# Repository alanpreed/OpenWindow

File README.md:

# OpenWindow
OpenWindow is a project that aims to create an open-source electric window controller for my car.

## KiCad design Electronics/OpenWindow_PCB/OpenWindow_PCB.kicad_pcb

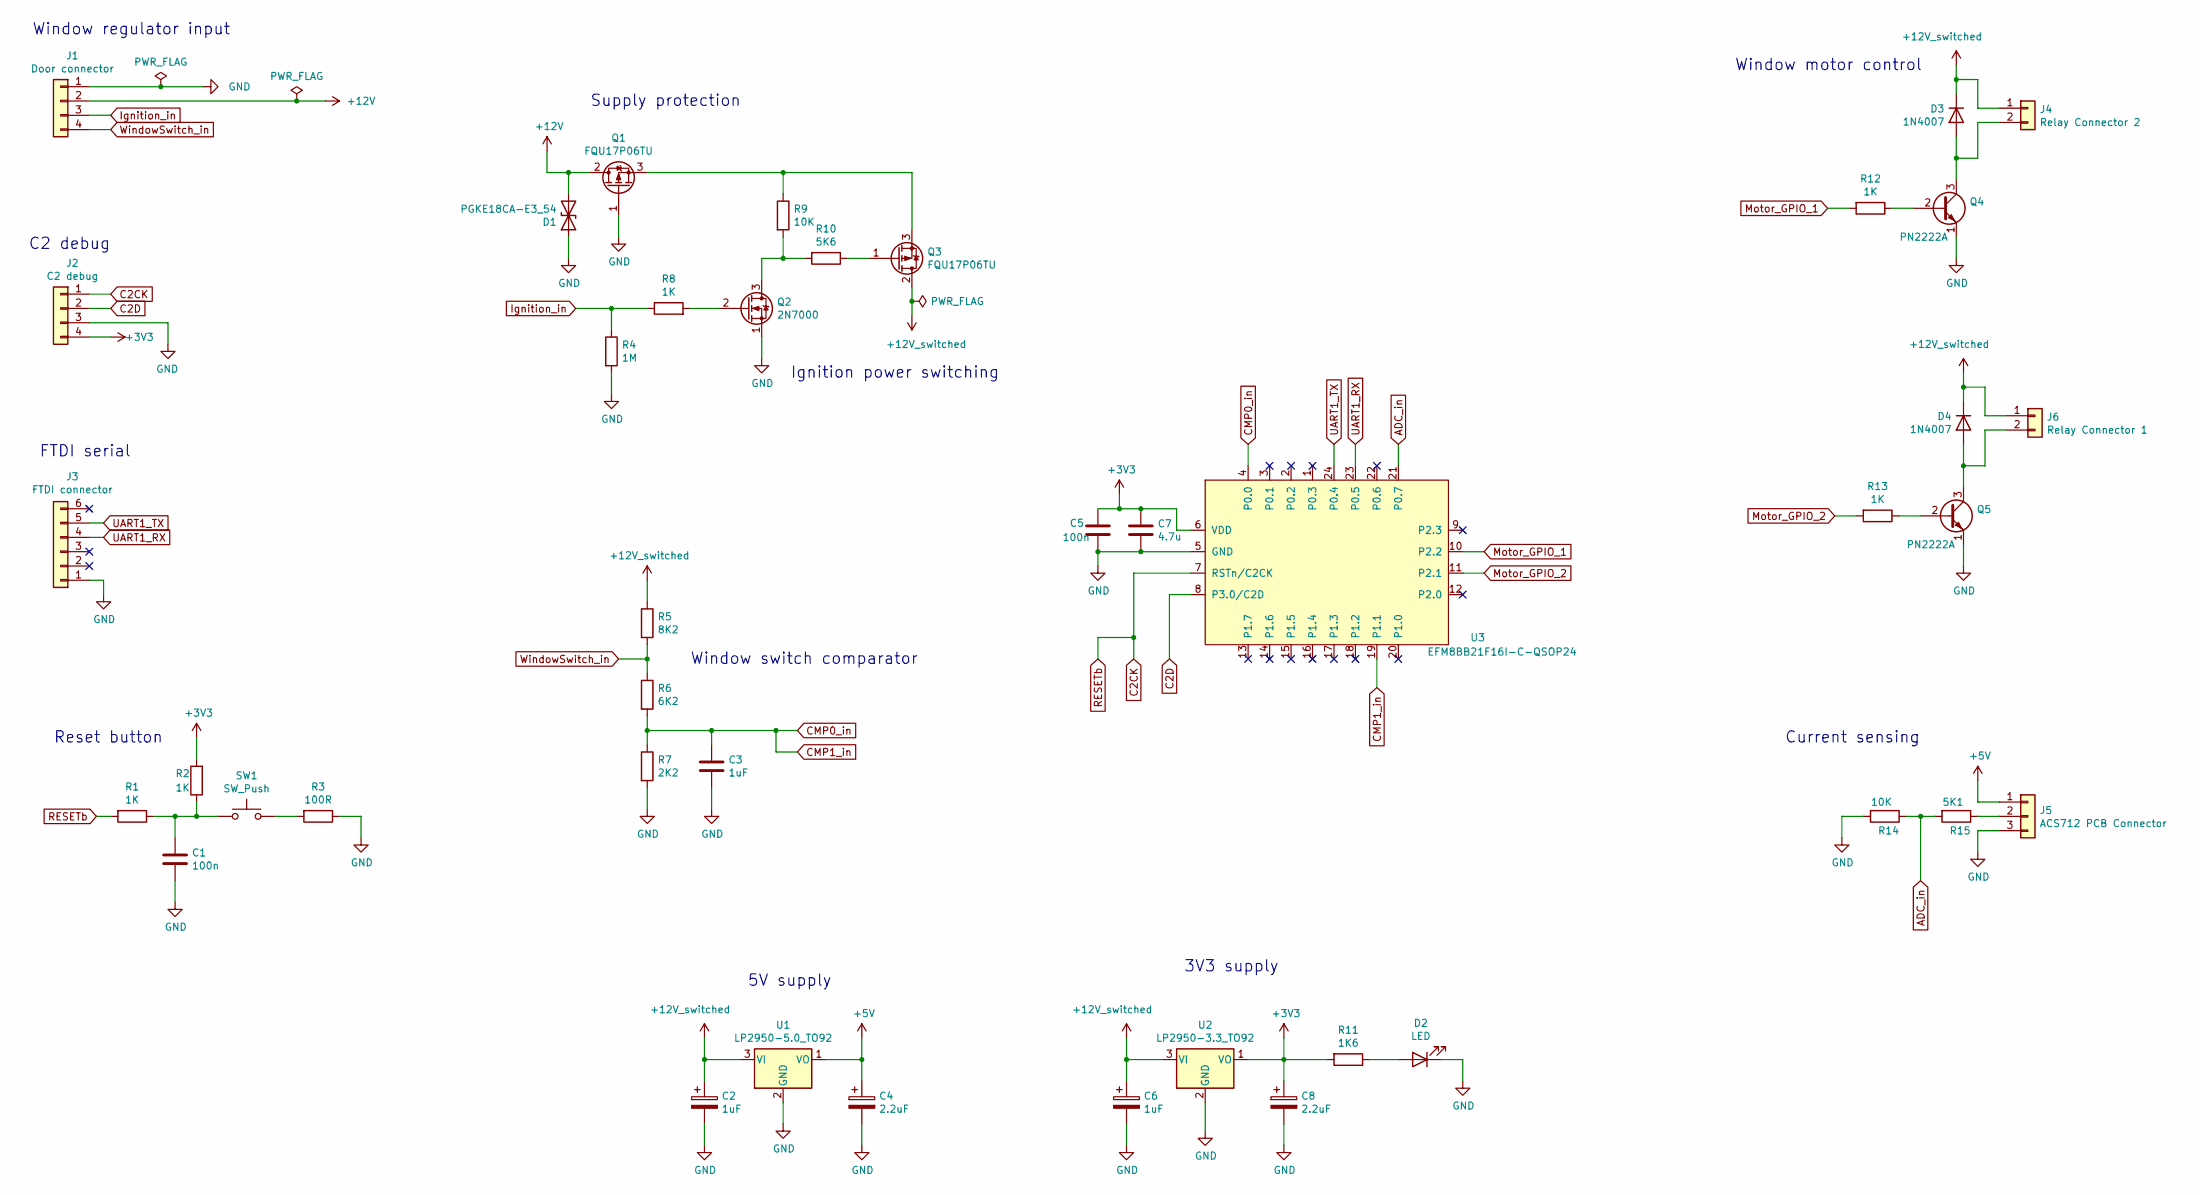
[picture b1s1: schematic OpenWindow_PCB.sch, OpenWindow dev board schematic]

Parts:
C1, C5: 100n; C_0805_2012Metric_Pad1.18x1.45mm_HandSolder
C2, C3, C6: 1uF; CP_Radial_D5.0mm_P2.00mm
C4, C8: 2.2uF; CP_Radial_D5.0mm_P2.00mm
C7: 4.7u; C_0805_2012Metric_Pad1.18x1.45mm_HandSolder
D1: PGKE18CA-E3_54; D_DO-15_P12.70mm_Horizontal
D2: LED; LED_D3.0mm
D3, D4: 1N4007; D_DO-41_SOD81_P10.16mm_Horizontal
J1: Door connector; JST_XH_B4B-XH-AM_1x04_P2.50mm_Vertical
J2: C2 debug; PinHeader_1x04_P2.54mm_Vertical
J3: FTDI connector; PinHeader_1x06_P2.54mm_Vertical
J4: Relay Connector 2; TerminalBlock_Phoenix_MKDS-3-2-5.08_1x02_P5.08mm_Horizontal
J5: ACS712 PCB Connector; JST_XH_B3B-XH-A_1x03_P2.50mm_Vertical
J6: Relay Connector 1; TerminalBlock_Phoenix_MKDS-3-2-5.08_1x02_P5.08mm_Horizontal
Q1, Q3: FQU17P06TU; TO-251-3_Vertical
Q2: 2N7000; TO-92_Inline
Q4, Q5: PN2222A; TO-92_Inline
R1, R2: 1K; R_0603_1608Metric_Pad0.98x0.95mm_HandSolder
R3: 100R; R_0603_1608Metric_Pad0.98x0.95mm_HandSolder
R4: 1M; R_Axial_DIN0411_L9.9mm_D3.6mm_P12.70mm_Horizontal
R5: 8K2; R_Axial_DIN0411_L9.9mm_D3.6mm_P12.70mm_Horizontal
R6: 6K2; R_Axial_DIN0411_L9.9mm_D3.6mm_P12.70mm_Horizontal
R7: 2K2; R_Axial_DIN0411_L9.9mm_D3.6mm_P12.70mm_Horizontal
R8, R12, R13: 1K; R_Axial_DIN0411_L9.9mm_D3.6mm_P12.70mm_Horizontal
R9, R14: 10K; R_Axial_DIN0411_L9.9mm_D3.6mm_P12.70mm_Horizontal
R10: 5K6; R_Axial_DIN0411_L9.9mm_D3.6mm_P12.70mm_Horizontal
R11: 1K6; R_Axial_DIN0411_L9.9mm_D3.6mm_P12.70mm_Horizontal
R15: 5K1; R_Axial_DIN0411_L9.9mm_D3.6mm_P12.70mm_Horizontal
SW1: SW_Push; SW_PUSH_6mm
U1: LP2950-5.0_TO92; TO-92_Inline
U2: LP2950-3.3_TO92; TO-92_Inline
U3: EFM8BB21F16I-C-QSOP24; QSOP-24_3.9x8.7mm_P0.635mm

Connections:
+3V3: C5.1, C7.1, C8.1, J2.4, R2.2, R11.2, U2.1 (VO), U3.6 (VDD)
+5V: C4.1, J5.1, U1.1 (VO)
+12V: D1.2 (A2), J1.2, Q1.2 (D)
+12V_switched: C2.1, C6.1, D3.1 (K), D4.1 (K), J4.1, J6.1, Q3.2 (D), R5.1, U1.3 (VI), U2.3 (VI)
ADC_in: R14.1, R15.2, U3.21 (P0.7)
C2CK: J2.1, R1.2, U3.7 (RSTn/C2CK)
C2D: J2.2, U3.8 (P3.0/C2D)
CMP0_in: C3.1, R6.2, R7.1, U3.4 (P0.0), U3.19 (P1.1)
GND: C1.2, C2.2, C3.2, C4.2, C5.2, C6.2, C7.2, C8.2, D1.1 (A1), D2.1 (K), J1.1, J2.3, J3.1, J5.3, Q1.1 (G), Q2.1 (S), Q4.1 (E), Q5.1 (E), R3.1, R4.2, R7.2, R14.2, U1.2 (GND), U2.2 (GND), U3.5 (GND)
Ignition_in: J1.3, R4.1, R8.1
Motor_GPIO_1: R12.2, U3.10 (P2.2)
Motor_GPIO_2: R13.2, U3.11 (P2.1)
unnamed: C1.1, R1.1, R2.1, SW1.1
unnamed: D2.2 (A), R11.1
unnamed: D3.2 (A), J4.2, Q4.3 (C)
unnamed: D4.2 (A), J6.2, Q5.3 (C)
unnamed: J5.2, R15.1
unnamed: Q1.3 (S), Q3.3 (S), R9.1
unnamed: Q2.2 (G), R8.2
unnamed: Q2.3 (D), R9.2, R10.2
unnamed: Q3.1 (G), R10.1
unnamed: Q4.2 (B), R12.1
unnamed: Q5.2 (B), R13.1
unnamed: R3.2, SW1.2
UART1_RX: J3.4, U3.23 (P0.5)
UART1_TX: J3.5, U3.24 (P0.4)
WindowSwitch_in: J1.4, R5.2, R6.1

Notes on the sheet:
Supply protection
Ignition power switching
5V supply
Window motor control
Window regulator input
FTDI serial
C2 debug
Window switch comparator
Current sensing
Reset button
3V3 supply

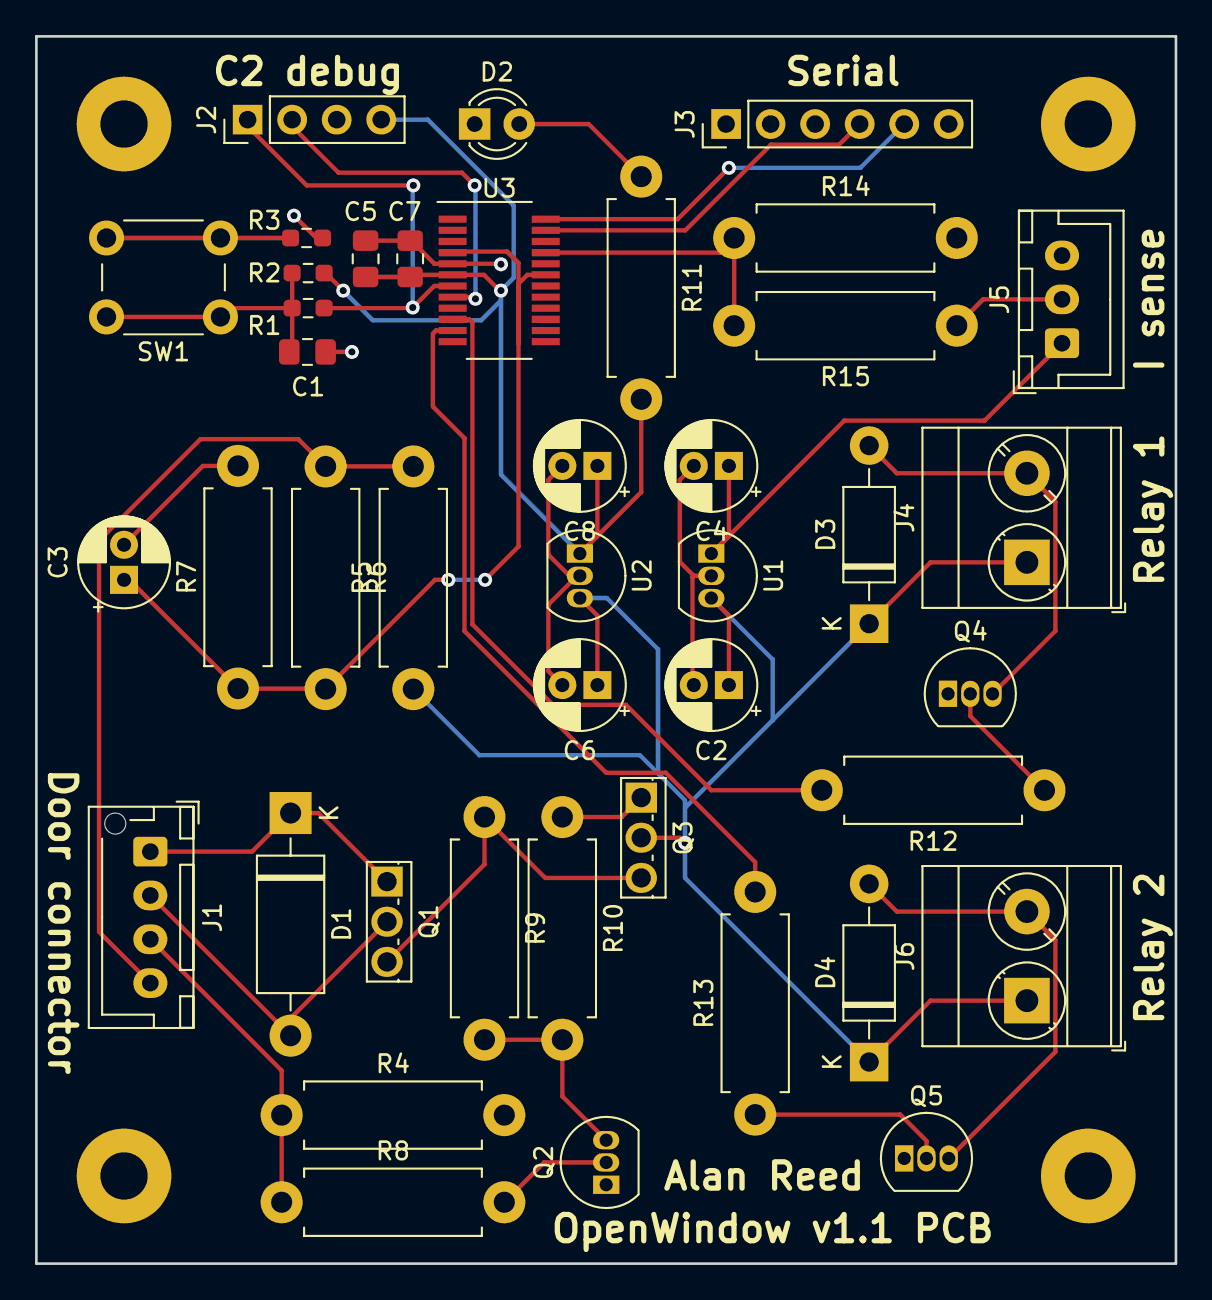
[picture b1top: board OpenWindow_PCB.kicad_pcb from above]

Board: 2 copper layers, 65.0 x 70.0 mm, 42 parts (0 on the bottom side), 27 nets.

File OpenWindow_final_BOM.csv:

Item, Quantity, Value, Footprint,URL
C2 C3 C6 ,3,1uF,Capacitor_THT:CP_Radial_D5.0mm_P2.00mm,~
C4 C8 ,2,2.2uF,Capacitor_THT:CP_Radial_D5.0mm_P2.00mm,~
C1 C5 ,2,100n,Capacitor_SMD:C_0805_2012Metric_Pad1.18x1.45mm_HandSolder,~
C7 ,1,4.7u,Capacitor_SMD:C_0805_2012Metric_Pad1.18x1.45mm_HandSolder,~
D1 ,1,PGKE18CA-E3_54,Diode_THT:D_DO-15_P12.70mm_Horizontal,http://www.farnell.com/datasheets/2049206.pdf
D2 ,1,LED,LED_THT:LED_D3.0mm,~
D3 D4 ,2,1N4007,Diode_THT:D_DO-41_SOD81_P10.16mm_Horizontal,http://www.vishay.com/docs/88503/1n4001.pdf
J1 ,1,Door connector,Connector_JST:JST_XH_B4B-XH-AM_1x04_P2.50mm_Vertical,~
J2 ,1,C2 connector,Connector_PinHeader_2.54mm:PinHeader_1x03_P2.54mm_Vertical,~
J3 ,1,FTDI connector,Connector_PinHeader_2.54mm:PinHeader_1x06_P2.54mm_Vertical,~
J4 ,1,Relay Connector 2,TerminalBlock_Phoenix:TerminalBlock_Phoenix_MKDS-3-2-5.08_1x02_P5.08mm_Horizontal,~
J5 ,1,ACS712 PCB Connector,Connector_JST:JST_XH_B3B-XH-A_1x03_P2.50mm_Vertical,~
J6 ,1,Relay Connector 1,TerminalBlock_Phoenix:TerminalBlock_Phoenix_MKDS-3-2-5.08_1x02_P5.08mm_Horizontal,~
Q2 ,1,2N7000,Package_TO_SOT_THT:TO-92_Inline,https://www.fairchildsemi.com/datasheets/2N/2N7000.pdf
Q1 Q3 ,2,FQU17P06TU,Package_TO_SOT_THT:TO-251-3_Vertical,http://www.farnell.com/datasheets/2304440.pdf
Q4 Q5 ,2,PN2222A,Package_TO_SOT_THT:TO-92_Inline,http://www.fairchildsemi.com/ds/PN/PN2222A.pdf
R1 R2 ,2,1K,Resistor_SMD:R_0603_1608Metric_Pad0.98x0.95mm_HandSolder,~
R10 ,1,5K6,Resistor_THT:R_Axial_DIN0411_L9.9mm_D3.6mm_P12.70mm_Horizontal,~
R11 ,1,1K6,Resistor_THT:R_Axial_DIN0411_L9.9mm_D3.6mm_P12.70mm_Horizontal,~
R15 ,1,5K1,Resistor_THT:R_Axial_DIN0411_L9.9mm_D3.6mm_P12.70mm_Horizontal,~
R3 ,1,100R,Resistor_SMD:R_0603_1608Metric_Pad0.98x0.95mm_HandSolder,~
R4 ,1,1M,Resistor_THT:R_Axial_DIN0411_L9.9mm_D3.6mm_P12.70mm_Horizontal,~
R5 ,1,8K2,Resistor_THT:R_Axial_DIN0411_L9.9mm_D3.6mm_P12.70mm_Horizontal,~
R6 ,1,6K2,Resistor_THT:R_Axial_DIN0411_L9.9mm_D3.6mm_P12.70mm_Horizontal,~
R7 ,1,2K2,Resistor_THT:R_Axial_DIN0411_L9.9mm_D3.6mm_P12.70mm_Horizontal,~
R8 R12 R13 ,3,1K,Resistor_THT:R_Axial_DIN0411_L9.9mm_D3.6mm_P12.70mm_Horizontal,~
R9 R14 ,2,10K,Resistor_THT:R_Axial_DIN0411_L9.9mm_D3.6mm_P12.70mm_Horizontal,~
SW1 ,1,SW_Push,Button_Switch_THT:SW_PUSH_6mm,~
U1 ,1,LP2950-5.0_TO92,Package_TO_SOT_THT:TO-92_Inline,http://www.ti.com/lit/ds/symlink/lp2951-n.pdf
U2 ,1,LP2950-3.3_TO92,Package_TO_SOT_THT:TO-92_Inline,http://www.ti.com/lit/ds/symlink/lp2950-n.pdf
U3 ,1,EFM8BB21F16I-C-QSOP24,Package_SO:QSOP-24_3.9x8.7mm_P0.635mm,
Motor relay,2,"Multicomp SPDT, 14VDC, 30A MCCMA31-DC12V-C",,
Relay socket,2,5 pin automotive relay socket,,https://www.ebay.co.uk/itm/Prewired-4-5-Pin-Automotive-Relay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
6-way terminal block,1,Minimum 20A,,https://uk.farnell.com/hylec/hyks-05712pp/terminal-block-bar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
Current measurement PCB,1,ACS712 20A current measurement PCB,,https://www.ebay.co.uk/itm/ACS712-20A-Hall-effect-isolated-A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
5 pin inline connector,1,VW 357 972 755 / 357 972 765,,https://www.aliexpress.com/item/4000075476089.html?spm=a2g0s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
2 pin inline connector,1,VW 357 972 762 / 357 972 752 ,,https://www.aliexpress.com/item/32457754886.html?spm=a2g0s.9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
JST XH  4 pin connector,1,,,
JST XH  3 pin connector,2,,,
Rubber grommet,1,3/8” x ½”,,
17mm m2.5 standoffs,4,,,https://cpc.farnell.com/ettinger/05-12-173/spacer-hex-m2-5x1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
M2.5 nuts,6,,,
M2.5 6mm bolts,4,,,
M2.5 12mm bolts,2,,,
Main PCB,1,,,
3D printed case,1,,,
3D printed lid,1,,,
3D printed current PCB clamp,1,,,
3D printed current PCB spacer,1,,,

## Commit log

2020-09-28 Created Simplicity Studio project
2020-09-29 Updated hardware configuration to enable UART1
2020-09-29 Added gitignore
2020-09-29 Updated hardware config
2020-09-29 Created basic data buffer
2020-09-29 Initial attempt at interrupt-driven UART driver
2020-09-29 Simplified so that TX interrupt is always enabled
2020-09-29 Confirgured comparator 0
2020-09-29 Configured comparator 1, updated comparator 2.
2020-09-29 Configured and tested pins for relay control
2020-10-05 Created interrupt-safe print function. Added initial ADC functionality
2020-10-05 Added comment
2020-10-06 Added linker control file to prevent interrupt function warnings
2020-10-08 Made print and buffer functions reentrant
2020-10-08 Removed reentrant functions from linker control file
2020-10-08 Created motor control
2020-10-08 Split CMP init to prevent interrupts on startup
2020-10-08 Created state machine
2020-10-09 Changed motor pins, enabled ADC timer trigger
2020-10-09 Completed ADC config and driver
2020-10-11 Created initial schematic
2020-10-13 Made state machine more tolerant of errors
2021-01-23 Minor schematic changes
2021-01-23 Set up Kicad project for PCB design
2021-01-27 Initial PCB layout
2021-03-17 Added PCB layout output files
2021-03-17 Updated build config for PCB instead of dev board
2021-03-17 Added CAD files for case and current PCB mounts
2021-03-17 Added missing description
2021-03-21 Added basic bill of materials
2021-03-21 Corrected C2 debug header
